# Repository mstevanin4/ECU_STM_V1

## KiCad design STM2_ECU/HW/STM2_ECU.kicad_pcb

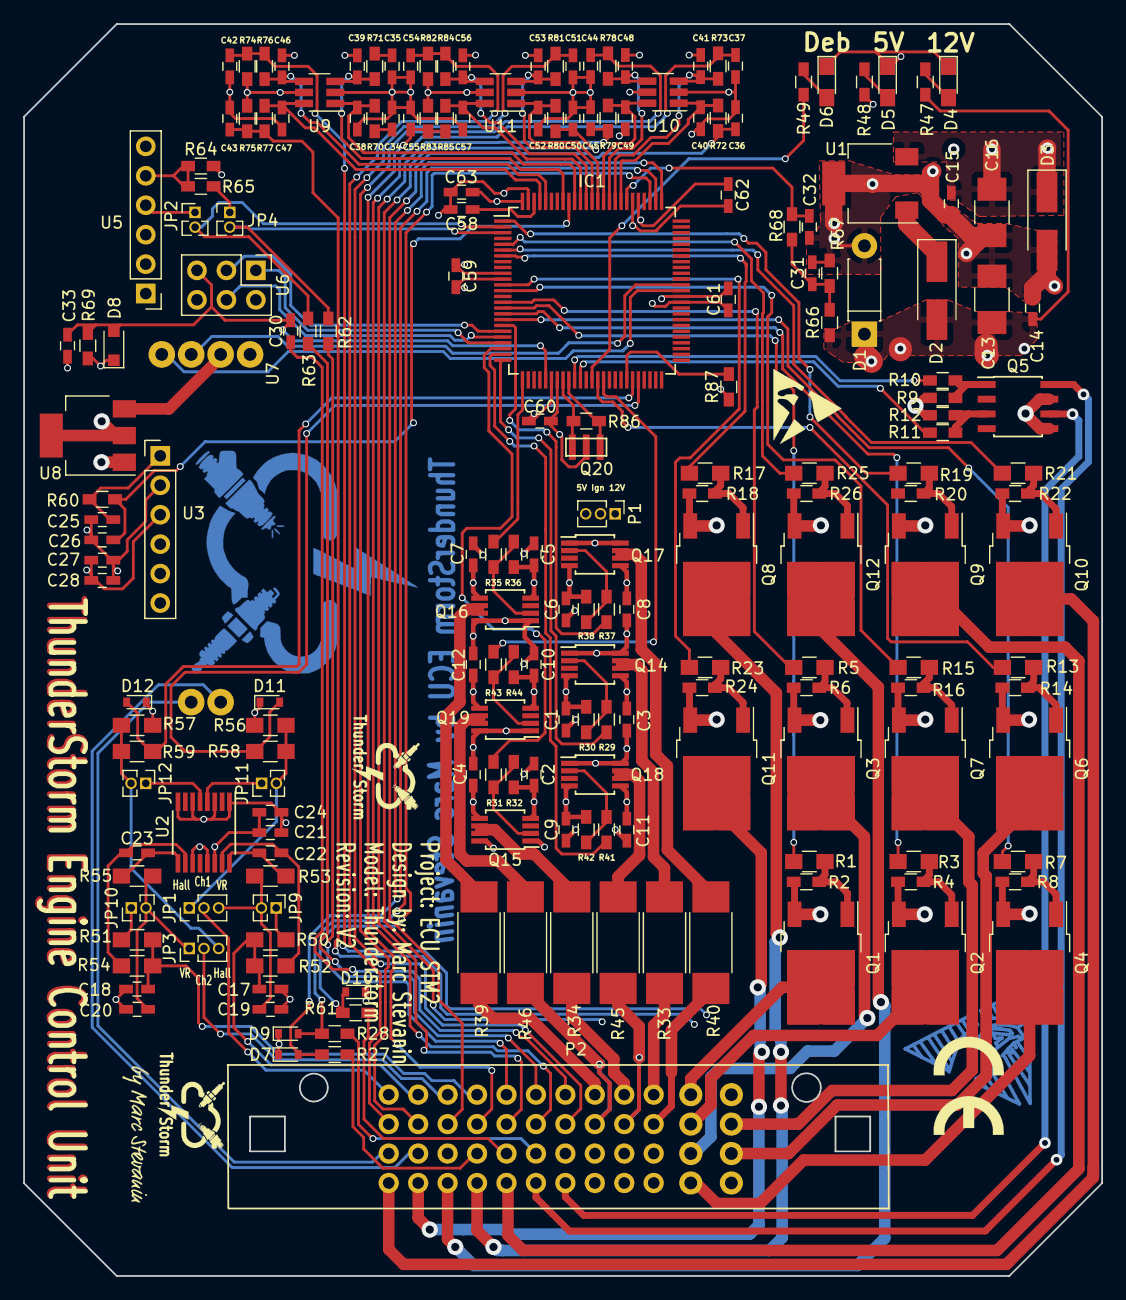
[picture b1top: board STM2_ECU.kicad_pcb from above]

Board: 4 copper layers, 93.0 x 108.0 mm, 201 parts (0 on the bottom side), 145 nets.

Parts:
C1, C2, C5, C6, C9, C10, C21, C28: 1uF; C_0603_HandSoldering
C3, C4, C7, C8, C11, C12, C14, C15, C24, C25, C26, C27, C30, C31, C34, C35, C36, C37, C42, C43, C44, C45, C50, C51, C54, C55, C58, C59, C60, C61, C62, C63: 100nF; C_0603_HandSoldering
C13: 10uF; C_1210_HandSoldering
C16: 47uF; C_1210_HandSoldering
C17, C18, C19, C20: 10nF; C_0603_HandSoldering
C22, C23: 1nF; C_0603_HandSoldering
C32, C38, C39, C40, C41, C46, C47, C48, C49, C52, C53, C56, C57: 220nF; C_0603_HandSoldering
C33: 4nF7; C_0603_HandSoldering
D1: ERZ-V14D220; D_DO-41_SOD81_P7.62mm_Horizontal
D2: B130-13-F; D_SMA_Handsoldering
D3: 3SMAJ5919B-TP; D_SMA_Handsoldering
D4, D5, D6: SML-211UTT86; LED_0805_HandSoldering
D7, D9, D10, D11, D12: CDBU00340; D_0603
D8: B0540WS-7; D_SOD-323_HandSoldering
IC1: ATMEGA2560-A_perso; TQFP-100_14x14mm_Pitch0.5mm
JP1, JP3: JUMPER3; Pin_Header_Straight_1x03_Pitch1.27mm
JP2, JP4, JP9, JP10, JP11, JP12: Jumper_NC_Small; Pin_Header_Straight_1x02_Pitch1.27mm
P1: CONN_01X03; Pin_Header_Straight_1x03_Pitch1.27mm
P2: Molex48p; Molex_Conn_48p
Q1, Q2, Q3, Q4, Q6, Q7, Q8, Q9, Q10, Q11, Q12: VDN5N07; TO-252-2
Q5: VNLD5090-E; SOIC-8_3.9x4.9mm_Pitch1.27mm
Q14, Q15, Q16, Q17, Q18, Q19: TC1413NEUA; MSOP-8_3x3mm_Pitch0.65mm
Q20: CSTCE16M0V53C-R0; 16MHz_Oscillator
R1, R3, R5, R7, R13, R15, R17, R19, R21, R23, R25, R58, R59: 1K; R_0805_HandSoldering
R2, R4, R6, R8, R9, R12, R14, R16, R18, R20, R22, R24, R26, R30, R32, R36, R38, R42, R44: 100K; R_0603_HandSoldering
R10, R11, R29, R31, R35, R37, R41, R43, R47, R62, R63, R65, R67, R69: 1K; R_0603_HandSoldering
R27, R28, R60, R61, R68, R70, R71, R72, R73, R76, R77, R78, R79, R80, R81, R84, R85: 470U; R_0603_HandSoldering
R33, R34, R39, R40, R45, R46: 15R; R_2512_HandSoldering
R48, R49: 680U; R_0603_HandSoldering
R50, R51, R52, R53, R54, R55, R56, R57: 10K; R_0805_HandSoldering
R64: 2K2; R_0603_HandSoldering
R66: 3K9; R_0603_HandSoldering
R74, R75, R82, R83: 2K49; R_0603_HandSoldering
R86: 1M; R_0603_HandSoldering
R87: 3K3; R_0603_HandSoldering
U1: LM2940IMP-5.0/NOPBCT-ND; SOT-223-3_TabPin2
U2: MAX9926UAEE; QSOP-16_3.9x4.9mm_Pitch0.635mm
U3: MPX4250AP; Pin_Header_Straight_1x06_Pitch2.54mm
U5: HC-06; Pin_Header_Straight_1x06_Pitch2.54mm
U6: ISP_terminal; Pin_Header_Straight_2x03_Pitch2.54mm
U7: Seeeduino_CAN-BUS_Module_MCP2551_and_MCP2515; Seeeduino_CAN_Module
U8: MCP1703A-3302E/DB; SOT-223-3_TabPin2
U9, U10, U11: SP724AHTG; SOT-23-6_Handsoldering

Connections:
+5V: C15.1, C16.1, C21.1, C24.1, C27.1, C28.1, C59.1, C60.1, C61.1, C62.1, C63.1, D3.1, D7.1, D8.1, D9.1, D10.1, D11.1, D12.1, IC1.10, IC1.31, IC1.61, IC1.80, IC1.100, P1.3, P2.G3, P2.H4, R48.1, R56.2, R57.2, R69.1, R74.2, R75.2, R82.2, R83.2, R87.1, U1.3, U2.14, U3.3, U5.2, U6.2, U8.1, U9.5, U10.5, U11.5
+12V: C13.1, C14.1, D1.1, D2.2, P1.1, P2.M4, R47.1, R66.1
/AnalogInputs/AI1: C51.1, P2.G2, R81.2
/AnalogInputs/AI1_CPU: C53.1, IC1.88, R81.1, U11.3
/AnalogInputs/AI2: C50.1, P2.H3, R80.2
/AnalogInputs/AI2_CPU: C52.1, IC1.87, R80.1, U11.1
/AnalogInputs/CLT: C54.1, P2.A2, R82.1, R84.2
/AnalogInputs/CLT_CPU: C56.1, IC1.89, R84.1, U11.4
/AnalogInputs/MAP_E: C45.1, P2.E2, R79.2
/AnalogInputs/MAP_E_CPU: C49.1, IC1.86, R79.1, U10.6
/AnalogInputs/MAT: C55.1, P2.D2, R83.1, R85.2
/AnalogInputs/MAT_CPU: C57.1, IC1.90, R85.1, U11.6
/AnalogInputs/O2_1: C36.1, P2.C2, R72.2
/AnalogInputs/O2_1_CPU: C40.1, IC1.83, R72.1, U10.1
/AnalogInputs/O2_2: C37.1, P2.F2, R73.2
/AnalogInputs/O2_2_CPU: C41.1, IC1.84, R73.1, U10.3
/AnalogInputs/PROT_RES1: C34.1, R70.2
/AnalogInputs/PROT_RES1_CPU: C38.1, IC1.91, R70.1, U9.1
/AnalogInputs/PROT_RES2: C35.1, R71.2
/AnalogInputs/PROT_RES2_CPU: C39.1, IC1.93, R71.1, U9.3
/AnalogInputs/TI1: C43.1, P2.J3, R75.1, R77.2
/AnalogInputs/TI1_CPU: C47.1, IC1.97, R77.1, U9.6
/AnalogInputs/TI2: C42.1, P2.K3, R74.1, R76.2
/AnalogInputs/TI2_CPU: C46.1, IC1.96, R76.1, U9.4
/AnalogInputs/TPS: C44.1, P2.B2, R78.2
/AnalogInputs/TPS_CPU: C48.1, IC1.85, R78.1, U10.4
/BattRefVolt/BRV_CPU: C32.1, IC1.82, R68.1
/BlueTooth/RX: JP2.1, U5.4
/BlueTooth/TX: JP4.1, R65.2
/CanBus/CANH: P2.A3, U7.6
/CanBus/CANL: P2.B3, U7.5
/CanBus/RX_CAN: IC1.63, U7.4
/CanBus/TX_CAN: IC1.64, U7.3
/Connectors/AUX1_DRV: P2.D4, Q8.2
/Connectors/BOOST: P2.B4, Q11.2
/Connectors/DIG_IO1: P2.E3, R61.2
/Connectors/DIG_IO2: P2.F3, R28.2
/Connectors/DTR_USB: C30.1, P2.G1
/Connectors/FAN: P2.E4, Q9.2
/Connectors/FP_DRV: P2.C4, Q12.2
/Connectors/IACA2: P2.A4, Q10.2
/Connectors/IACB1: P2.G4, Q5.6
/Connectors/IACB2: P2.F4, Q5.8
/Connectors/IGN1: P2.K1, R33.1
/Connectors/IGN2: P2.J1, R34.1
/Connectors/IGN3: P2.H1, R39.1
/Connectors/IGN4: P2.K2, R40.1
/Connectors/IGN5: P2.J2, R45.1
/Connectors/IGN6: P2.H2, R46.1
/Connectors/INJ1: P2.L1, Q1.2
/Connectors/INJ2: P2.L2, Q2.2
/Connectors/INJ3: P2.L3, Q3.2
/Connectors/INJ4: P2.L4, Q4.2
/Connectors/INJ5: P2.M2, Q7.2
/Connectors/INJ6: P2.M3, Q6.2
/Connectors/RDX_USB: P2.E1, R62.1
/Connectors/TACHO: P2.D3, R27.2
/Connectors/TXD_USB: P2.F1, R63.1
/Connectors/VR1+: JP1.2, P2.A1
/Connectors/VR1-: C17.1, P2.B1, R50.2, R52.2
/Connectors/VR2+: JP3.2, P2.C1
/Connectors/VR2-: C18.1, P2.D1, R51.2, R54.2
/CrkCam/TACH1_CPU: D11.2, IC1.46, R58.1
/CrkCam/TACH2_CPU: D12.2, IC1.45, R59.1
/ISP/MISO: IC1.22, U6.1
/ISP/MOSI: IC1.21, U6.4
/ISP/RESET_CPU: C30.2, C33.1, D8.2, IC1.30, R69.2, U6.5
/ISP/SCK: IC1.20, U6.3
/IgnOut/IGN1_CPU: IC1.25, R29.2
/IgnOut/IGN2_CPU: IC1.23, R31.2
/IgnOut/IGN3_CPU: IC1.26, R35.2
/IgnOut/IGN4_CPU: IC1.19, R37.2
/IgnOut/IGN5_CPU: IC1.24, R41.2
/IgnOut/IGN6_CPU: IC1.40, R43.2
/IntMap/MAP_I_CPU: C26.1, IC1.92, R60.2
/LEDs/DEBUG_CPU: IC1.38, R49.1
/PwrOut/AUX1_CPU: IC1.7, R17.2
/PwrOut/AUX3_CPU: IC1.6, R21.2
/PwrOut/BOOST_CPU: IC1.12, R23.2
/PwrOut/DIR_CPU: IC1.36, R11.2
/PwrOut/FAN_CPU: IC1.1, R19.2
/PwrOut/FP_CPU: IC1.5, R25.2
/PwrOut/INJ1_CPU: IC1.16, R1.2
/PwrOut/INJ2_CPU: IC1.17, R3.2
/PwrOut/INJ3_CPU: IC1.15, R5.2
/PwrOut/INJ4_CPU: IC1.18, R7.2
/PwrOut/INJ5_CPU: IC1.13, R15.2
/PwrOut/INJ6_CPU: IC1.39, R13.2
/PwrOut/STEP_CPU: IC1.35, R10.2
/UsbCom/RX: IC1.2, JP2.2, R63.2
/UsbCom/TX: IC1.3, JP4.2, R62.2
/uC_level/FLEX_CPU: IC1.44, R87.2
GND: C1.2, C2.2, C3.2, C4.2, C5.2, C6.2, C7.2, C8.2, C9.2, C10.2, C11.2, C12.2, C13.2, C14.2, C15.2, C16.2, C17.2, C18.2, C19.2, C20.2, C21.2, C24.2, C25.2, C26.2, C27.2, C28.2, C31.2, C32.2, C33.2, C34.2, C35.2, C36.2, C37.2, C38.2, C39.2, C40.2, C41.2, C42.2, C43.2, C44.2, C45.2, C46.2, C47.2, C48.2, C49.2, C50.2, C51.2, C52.2, C53.2, C54.2, C55.2, C56.2, C57.2, C58.2, C59.2, C60.2, C61.2, C62.2, C63.2, D1.2, D3.2, D4.1, D5.1, D6.1, IC1.11, IC1.32, IC1.62, IC1.81, IC1.99, P2.C3, P2.M1, Q1.3, Q2.3, Q3.3, Q4.3, Q5.5, Q5.7, Q6.3, Q7.3, Q8.3, Q9.3, Q10.3, Q11.3, Q12.3, Q14.4, Q14.5, Q15.4, Q15.5, Q16.4, Q16.5, Q17.4, Q17.5, Q18.4, Q18.5, Q19.4, Q19.5, Q20.3, R2.2, R4.2, R6.2, R8.2, R9.2, R12.2, R14.2, R16.2, R18.2, R20.2, R22.2, R24.2, R26.2, R30.2, R32.2, R36.2, R38.2, R42.2, R44.2, R64.2, R67.2, U1.2, U2.1, U2.3, U2.6, U2.8, U2.11, U2.13, U3.2, U5.3, U6.6, U7.1, U8.2, U9.2, U10.2, U11.2
unnamed: C19.1, JP1.3, JP9.2, R53.2
unnamed: C20.1, JP3.1, JP10.2, R55.2
unnamed: C22.1, R52.1, U2.15
unnamed: C22.2, R53.1, U2.16
unnamed: C23.1, R54.1, U2.10
unnamed: C23.2, R55.1, U2.9
unnamed: C25.1, R60.1, U3.1
unnamed: C31.1, R66.2, R67.1, R68.2
unnamed: C58.1, IC1.98
unnamed: D2.1, U1.1
unnamed: D4.2, R47.2
unnamed: D5.2, R48.2
unnamed: D6.2, R49.2
unnamed: D7.2, IC1.76, R27.1
unnamed: D9.2, IC1.77, R28.1
unnamed: D10.2, IC1.78, R61.1
unnamed: IC1.33, Q20.1, R86.1
unnamed: IC1.34, Q20.2, R86.2
unnamed: JP1.1, JP11.2, R56.1, R58.2
unnamed: JP9.1, R50.1
unnamed: JP10.1, R51.1
unnamed: JP11.1, U2.4
unnamed: JP12.1, U2.5
unnamed: JP3.3, JP12.2, R57.1, R59.2
unnamed: Q1.1, R1.1, R2.1
unnamed: Q2.1, R3.1, R4.1
unnamed: Q3.1, R5.1, R6.1
unnamed: Q4.1, R7.1, R8.1
unnamed: Q5.1, R9.1, R10.1
unnamed: Q5.3, R11.1, R12.1
unnamed: Q6.1, R13.1, R14.1
unnamed: Q7.1, R15.1, R16.1
unnamed: Q8.1, R17.1, R18.1
unnamed: Q9.1, R19.1, R20.1
unnamed: Q10.1, R21.1, R22.1
unnamed: Q11.1, R23.1, R24.1
unnamed: Q12.1, R25.1, R26.1
unnamed: Q14.2, R29.1, R30.1
unnamed: Q14.6, Q14.7, R33.2
unnamed: Q15.2, R31.1, R32.1
unnamed: Q15.6, Q15.7, R34.2
unnamed: Q16.2, R35.1, R36.1
unnamed: Q16.6, Q16.7, R39.2
unnamed: Q17.2, R37.1, R38.1
unnamed: Q17.6, Q17.7, R40.2
unnamed: Q18.2, R41.1, R42.1
unnamed: Q18.6, Q18.7, R45.2
unnamed: Q19.2, R43.1, R44.1
unnamed: Q19.6, Q19.7, R46.2
unnamed: R64.1, R65.1, U5.5
unnamed: U7.2, U8.3
V_IGN: C1.1, C2.1, C3.1, C4.1, C5.1, C6.1, C7.1, C8.1, C9.1, C10.1, C11.1, C12.1, P1.2, Q14.1, Q14.8, Q15.1, Q15.8, Q16.1, Q16.8, Q17.1, Q17.8, Q18.1, Q18.8, Q19.1, Q19.8

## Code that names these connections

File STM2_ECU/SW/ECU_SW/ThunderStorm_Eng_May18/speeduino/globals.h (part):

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#define BIT_ENGINE_CRANK    1   // Engine cranking
#define BIT_ENGINE_ASE      2   // after start enrichment (ASE)
#define BIT_ENGINE_WARMUP   3   // Engine in warmup
#define BIT_ENGINE_ACC      4   // in acceleration mode (TPS accel)
#define BIT_ENGINE_DCC      5   // in deceleration mode
#define BIT_ENGINE_MAPACC   6   // MAP acceleration mode
#define BIT_ENGINE_MAPDCC   7   // MAP decelleration mode

//Define masks for Status1
#define BIT_STATUS1_INJ1           0  //inj1
#define BIT_STATUS1_INJ2           1  //inj2
#define BIT_STATUS1_INJ3           2  //inj3
#define BIT_STATUS1_INJ4           3  //inj4
#define BIT_STATUS1_DFCO           4 //Decelleration fuel cutoff
#define BIT_STATUS1_BOOSTCUT       5  //Fuel component of MAP based boost cut out
#define BIT_STATUS1_TOOTHLOG1READY 6  //Used to flag if tooth log 1 is ready
#define BIT_STATUS1_TOOTHLOG2READY 7  //Used to flag if tooth log 2 is ready (Log is not currently used)

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#define BIT_SPARK_SLAUNCH         1  //Soft Launch indicator
#define BIT_SPARK_HRDLIM          2  //Hard limiter indicator
#define BIT_SPARK_SFTLIM          3  //Soft limiter indicator
#define BIT_SPARK_BOOSTCUT        4  //Spark component of MAP based boost cut out
#define BIT_SPARK_ERROR           5  // Error is detected
#define BIT_SPARK_IDLE            6  // idle on
#define BIT_SPARK_SYNC            7  // Whether engine has sync or not
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  byte wueValues[10]; //Warm up enrichment array (10 bytes)
  byte crankingPct; //Cranking enrichment
  byte pinMapping; // The board / ping mapping to be used
  byte tachoPin : 6; //Custom pin setting for tacho output
  byte tachoDiv : 2; //Whether to change the tacho speed
  byte unused2_17;
  byte unused2_18;
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byte pinTrigger; //The CAS pin
byte pinTrigger2; //The Cam Sensor pin
byte pinTrigger3;	//the 2nd cam sensor pin
byte pinTPS;//TPS input pin
byte pinMAP; //MAP sensor pin
byte pinEMAP; //EMAP sensor pin
byte pinMAP2; //2nd MAP sensor (Currently unused)
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byte pinO2_2; //second O2 pin
byte pinBat; //Battery voltage pin
byte pinDisplayReset; // OLED reset pin
byte pinTachOut; //Tacho output
byte pinFuelPump; //Fuel pump on/off
byte pinIdle1; //Single wire idle control
byte pinIdle2; //2 wire idle control (Not currently used)
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byte pinBoost;
byte pinVVT_1;		// vvt output 1
byte pinVVt_2;		// vvt output 2
byte pinFan;       // Cooling fan output
byte pinStepperDir; //Direction pin for the stepper motor driver
byte pinStepperStep; //Step pin for the stepper motor driver
byte pinStepperEnable; //Turning the DRV8825 driver on/off
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
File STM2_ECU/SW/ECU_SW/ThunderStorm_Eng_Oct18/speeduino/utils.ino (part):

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      pinCoil5 = 14; //Pin for coil 5
      pinTrigger = 2; //The CAS pin
      pinTrigger2 = 3; //The CAS pin
      pinTPS = A0; //TPS input pin
      pinMAP = A1; //MAP sensor pin
      pinIAT = A2; //IAT sensor pin
      pinCLT = A3; //CLS sensor pin
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      pinIdle2 = 47; //2 wire idle control
      pinStepperDir = 16; //Direction pin  for DRV8825 driver
      pinStepperStep = 17; //Step pin for DRV8825 driver
      pinFan = 47; //Pin for the fan output
      pinFuelPump = 4; //Fuel pump output
      pinTachOut = 49; //Tacho output pin
      pinFlex = 19; // Flex sensor (Must be external interrupt enabled)
      pinResetControl = 43; //Reset control output
    #endif
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      pinCoil5 = 34; //Pin for coil 5 PLACEHOLDER value for now
      pinTrigger = 20; //The CAS pin
      pinTrigger2 = 21; //The Cam Sensor pin
      pinTPS = A2; //TPS input pin
      pinMAP = A3; //MAP sensor pin
      pinIAT = A0; //IAT sensor pin
      pinCLT = A1; //CLS sensor pin
      pinO2 = A8; //O2 Sensor pin
      pinBat = A4; //Battery reference voltage pin
      pinDisplayReset = 48; // OLED reset pin
      pinTachOut = 49; //Tacho output pin
      pinIdle1 = 30; //Single wire idle control
      pinIdle2 = 31; //2 wire idle control
      pinStepperDir = 16; //Direction pin  for DRV8825 driver
      pinStepperStep = 17; //Step pin for DRV8825 driver
      pinFan = 47; //Pin for the fan output
      pinFuelPump = 4; //Fuel pump output
      pinFlex = 2; // Flex sensor (Must be external interrupt enabled)
      pinResetControl = 43; //Reset control output
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      pinCoil5 = 34; //Pin for coil 5 PLACEHOLDER value for now
      pinTrigger = 19; //The CAS pin
      pinTrigger2 = 18; //The Cam Sensor pin
      pinTPS = A2;//TPS input pin
      pinMAP = A3; //MAP sensor pin
      pinIAT = A0; //IAT sensor pin
      pinCLT = A1; //CLS sensor pin
      pinO2 = A8; //O2 Sensor pin
      pinBat = A4; //Battery reference voltage pin
      pinDisplayReset = 48; // OLED reset pin
      pinTachOut = 49; //Tacho output pin
      pinIdle1 = 5; //Single wire idle control
      pinIdle2 = 53; //2 wire idle control
      pinBoost = 7; //Boost control
      pinVVT_1 = 6; //Default VVT output
      pinFuelPump = 4; //Fuel pump output
      pinStepperDir = 16; //Direction pin  for DRV8825 driver
      pinStepperStep = 17; //Step pin for DRV8825 driver
      pinStepperEnable = 26; //Enable pin for DRV8825
      pinFan = A13; //Pin for the fan output
      pinLaunch = 51; //Can be overwritten below
      pinFlex = 2; // Flex sensor (Must be external interrupt enabled)
      pinResetControl = 50; //Reset control output
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      pinCoil5 = 34; //Pin for coil 5 PLACEHOLDER value for now
      pinTrigger = 19; //The CAS pin
      pinTrigger2 = 18; //The Cam Sensor pin
      pinTPS = A2;//TPS input pin
      pinMAP = A3; //MAP sensor pin
      pinIAT = A0; //IAT sensor pin
      pinCLT = A1; //CLS sensor pin
      pinO2 = A8; //O2 Sensor pin
      pinBat = A4; //Battery reference voltage pin
      pinDisplayReset = 48; // OLED reset pin
      pinTachOut = 49; //Tacho output pin  (Goes to ULN2803)
      pinIdle1 = 5; //Single wire idle control
      pinIdle2 = 6; //2 wire idle control
      pinBoost = 7; //Boost control
      pinVVT_1 = 4; //Default VVT output
      pinFuelPump = 45; //Fuel pump output  (Goes to ULN2803)
      pinStepperDir = 16; //Direction pin  for DRV8825 driver
      pinStepperStep = 17; //Step pin for DRV8825 driver
      pinStepperEnable = 24; //Enable pin for DRV8825
      pinFan = 47; //Pin for the fan output (Goes to ULN2803)
      pinLaunch = 51; //Can be overwritten below
      pinFlex = 2; // Flex sensor (Must be external interrupt enabled)
      pinResetControl = 43; //Reset control output
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        pinCoil3 = PB7; //Pin for coil 3
        pinCoil4 = PB8; //Pin for coil 4
        pinCoil5 = PB9; //Pin for coil 5
        pinTPS = A0; //TPS input pin
        pinMAP = A1; //MAP sensor pin
        pinIAT = A2; //IAT sensor pin
        pinCLT = A3; //CLT sensor pin
        pinO2 = A4; //O2 Sensor pin
        pinBat = A5; //Battery reference voltage pin
        pinBaro = A10;
        pinIdle1 = PB8; //Single wire idle control
        pinIdle2 = PB9; //2 wire idle control
        pinBoost = PE0; //Boost control
        pinVVT_1 = PE1; //Default VVT output
        pinStepperDir = PD8; //Direction pin  for DRV8825 driver
        pinStepperStep = PB15; //Step pin for DRV8825 driver
        pinStepperEnable = PD9; //Enable pin for DRV8825
        pinDisplayReset = PE1; // OLED reset pin
        pinFan = PE2; //Pin for the fan output
        pinFuelPump = PA6; //Fuel pump output
        pinTachOut = PA7; //Tacho output pin
        //external interrupt enabled pins
        //external interrupts could be enalbed in any pin, except same port numbers (PA4,PE4)
        pinFlex = PE2; // Flex sensor (Must be external interrupt enabled)
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        pinCoil3 = PA14; //Pin for coil 3
        pinCoil4 = PA9; //Pin for coil 4
        pinCoil5 = PA8; //Pin for coil 5
        pinTPS = A0; //TPS input pin
        pinMAP = A1; //MAP sensor pin
        pinIAT = A2; //IAT sensor pin
        pinCLT = A3; //CLS sensor pin
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        pinBaro = pinMAP;
        pinIdle1 = PB2; //Single wire idle control
        pinIdle2 = PA2; //2 wire idle control
        pinBoost = PA1; //Boost control
        pinVVT_1 = PA0; //Default VVT output
        pinStepperDir = PC15; //Direction pin  for DRV8825 driver
        pinStepperStep = PC14; //Step pin for DRV8825 driver
        pinStepperEnable = PC13; //Enable pin for DRV8825
        pinDisplayReset = PB2; // OLED reset pin
        pinFan = PB1; //Pin for the fan output
        pinFuelPump = PB11; //Fuel pump output
        pinTachOut = PB10; //Tacho output pin
        //external interrupt enabled pins
        pinFlex = PB8; // Flex sensor (Must be external interrupt enabled)
        pinTrigger = PA10; //The CAS pin
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      pinCoil5 = 11; //Pin for coil 5 PLACEHOLDER value for now
      pinTrigger = 18; //The CAS pin
      pinTrigger2 = 19; //The Cam Sensor pin
      pinTPS = A12;//TPS input pin
      pinMAP = A5; //MAP sensor pin
      pinIAT = A7; //IAT sensor pin
      pinCLT = A8; //CLS sensor pin
      pinO2 = A14; //O2 Sensor pin
      pinBat = A15; //Battery reference voltage pin
      //pinDisplayReset = A13; // OLED reset pin NOT DEFINE ECU_STM2!!!
      pinTachOut = 24; //Tacho output pin  (Goes to ULN2803)
      pinIdle1 = 48; //Single wire idle control !!changed ECU_STM2!!!
      pinIdle2 = 49; //2 wire idle control !! changed ECU_STM2!!!
      pinBoost = 17; //Boost control changed for ECU_STM2
      pinVVT_1 = 3; //Put on "AUX1_DRV" NOT DEFINE ECU_STM2!!!
      pinFuelPump = 5; //Fuel pump output
      //pinStepperDir = 48; //Direction pin  for DRV8825 driver
      //pinStepperStep = 49; //Step pin for DRV8825 driver
      //pinStepperEnable = 24; //Enable pin for DRV8825
      pinFan = 4; //Pin for the fan output (Goes to ULN2803)
      pinLaunch = 22; //Can be overwritten below ECU_STM2 
      pinFlex = 20; // Flex sensor (Must be external interrupt enabled) // ECU_STM2    
      break;
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      pinCoil5 = 34; //Pin for coil 5 PLACEHOLDER value for now
      pinTrigger = 19; //The CAS pin
      pinTrigger2 = 18; //The Cam Sensor pin
      pinTPS = A2;//TPS input pin
      pinMAP = A5; //MAP sensor pin
      pinIAT = A0; //IAT sensor pin
      pinCLT = A1; //CLS sensor pin
      pinO2 = A3; //O2 Sensor pin
      pinBat = A4; //Battery reference voltage pin
      pinDisplayReset = 48; // OLED reset pin
      pinTachOut = 49; //Tacho output pin  (Goes to ULN2803)
      pinIdle1 = 2; //Single wire idle control
      pinBoost = 4;
      pinIdle2 = 4; //2 wire idle control (Note this is shared with boost!!!)
      pinFuelPump = 37; //Fuel pump output
      pinStepperDir = 16; //Direction pin  for DRV8825 driver
      pinStepperStep = 17; //Step pin for DRV8825 driver
      pinFan = 35; //Pin for the fan output
      pinLaunch = 12; //Can be overwritten below
      pinFlex = 3; // Flex sensor (Must be external interrupt enabled)
      pinResetControl = 44; //Reset control output
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      pinCoil5 = 34; //Pin for coil 5 PLACEHOLDER value for now
      pinTrigger = 18; //The CAS pin
      pinTrigger2 = 19; //The Cam Sensor pin
      pinTPS = A2;//TPS input pin
      pinMAP = A3; //MAP sensor pin
      pinMAP2 = A8; //MAP2 sensor pin
      pinIAT = A0; //IAT sensor pin
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      pinDisplayReset = 48; // OLED reset pin
      pinSpareTemp1 = A6;
      pinSpareTemp2 = A5;
      pinTachOut = 41; //Tacho output pin transistori puuttuu 2n2222 tähän ja 1k 12v
      pinFuelPump = 42; //Fuel pump output 2n2222
      pinFan = 47; //Pin for the fan output
      pinTachOut = 49; //Tacho output pin
      pinFlex = 2; // Flex sensor (Must be external interrupt enabled)
      pinResetControl = 26; //Reset control output

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      pinO2 = A8; //O2 Sensor pin
      pinBat = A4; //Battery reference voltage pin
      pinMAP = A3; //MAP sensor pin
      pinTPS = A2;//TPS input pin
      pinCLT = A1; //CLS sensor pin
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
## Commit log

2018-04-17 commit HW as produced
    First 10 units produced, this is the HW side of the project at first production
2018-04-26 improvement of silkcreen references position for manufacturer
2018-05-02 add two projects of embedded SW (ECU engine and TestBench) and 2 tunerstudio projects (ECU engine and TestBench)
2018-05-09 New dashboard for Tunerstudio
2018-05-09 picture of ECU
2018-05-09 Add April18 update and create my one branch ThunderStorm_ECU_Eng
2018-06-10 First working setup for testbench
    Mass on cell is accurate within TunerStudio But calculated Torque looks like overflows
2018-08-09 changes for Test bench more or less working
2018-08-09 commit addd global repo
2018-08-09 before change
2018-08-10 new output PWM at High frequency on LED and on IGN6
2018-08-10 Speed controller added first version
2018-08-10 after test working setup, filter might be remove after spd hardware repair
2018-08-11 EngSpdSp ramp added filter on speed removed not tested
2018-10-11 Add a marketing flyer to project
2018-12-26 Add October SW Working version
2019-10-22 update HW files
2019-10-22 Create speeduino-201902b.zip
    Add backup february
2019-10-22 Repo clean up and add Trunk repo
2019-10-22 clean up 2
2019-10-22 update to code of september
2019-10-22 Update to September code to be tested
2019-10-22 change file name
2019-10-22 Report change of AFR target
2019-12-03 Add CAM sync to 36-2-2-2 decoder
2020-01-21 change limition for 360 to 720 deg for injector close angle
2020-05-13 before expertise subaru
2020-08-27 Update to august 2020 firmware
2020-08-27 add secSync variable
2020-08-28 change to PID close loop
2020-08-31 ädd fuel pressure signal and gauge
2020-08-31 remove second signature (compatibility with MSDroid)
2020-08-31 Add oil pressure in bar and replace Kpa by Bar for fuel pressure
2020-09-08 improve 36-222 for sequential use
2021-03-10 update little forget
2021-03-10 bug fix fuelpressure in ini file
2021-03-11 Update init.ino to support stepper motor as well as pwm valve
2021-09-07 try to improve subaru 6/7 decoder
2022-05-05 add ability to have afrtargetload different than VEmap
2024-08-07 before SW202402
2024-08-07 SW update to 202402
2025-07-27 add speeduino 202501_4
2025-10-18 change last sW

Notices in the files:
STM2_ECU/SW/ECU_SW/ThunderStorm_Eng_Oct18/speeduino/utils.ino:
Copyright (C) Josh Stewart
